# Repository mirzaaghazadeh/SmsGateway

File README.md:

# SmsGateway

**English** · [فارسی](README.fa.md)

A DIY two-SIM **SMS and missed-call gateway**: an ESP32-S3 with two SIM800L GSM modules in a
3D-printed, screwless case, plus a self-hosted Node.js server with a web panel. Build it the way
that suits you: **v1** is hand-wired in a printed case, **v2** puts everything on a PCB in its own
printed case.

| v1: 3D print + hand wiring | v2: PCB + 3D print |
|---|---|
|  |  |

All case images are rendered from the OpenSCAD source in `source/`.

## The idea

This is a hobby project. I carried the idea around for about three years before I finally sat
down and started building it.

It started with a very ordinary problem. After moving to another country, I kept two SIM cards
from home only to receive messages: bank and login codes (OTP), notices, and the odd missed call.
That meant carrying an old phone around just for them, remembering to charge it, and finding its
SMS inbox full at the worst moment, with a code that never arrived.

So I built this for myself: put the SIM cards in one small box that stays plugged in at home and
takes care of them:

- Every SMS that arrives on either SIM goes over Wi-Fi to **your own server**, and so does every
  incoming call (rejected and logged as a missed call).
- You read everything in a **web panel from anywhere**: verification codes, bank messages, who called.
- Or get them in **Telegram**: each SIM can go to its own chats, a one-time code is one tap to copy,
  and a reply to an SMS goes back to its sender from the same SIM. `/stats` answers with the status,
  `/balance` with the balance, and you get an alert when the gateway goes offline or a SIM loses
  the network.
- The SIM cards stay alive: the gateway can check their balance and send an SMS now and then, so
  the operator does not switch off a prepaid SIM that is rarely used. A SIM that is roaming can be
  set to cost nothing: calls ring instead of being hung up, and it sends no SMS.
- Your own apps can **send SMS** through a small HTTP API, or get a **webhook** the moment a
  message arrives.
- It is built from cheap off-the-shelf parts (an ESP32 and two SIM800L modules) in a 3D-printed
  case, and the server is self-hosted: no SMS service subscription, and no third party reading
  your messages.
- The SIM cards never fill up: each SMS is deleted from the card once the server has it.

Later I added what others would need too, so anyone can build one: for the same reason (SIM cards
from another country, codes you must not miss), or simply as a small self-hosted SMS gateway for
their own apps, with the HTTP API, webhooks and Telegram.

## Features

- **Two SIM cards**, each on its own SIM800L, cards slide in from the outside through the front wall.
- **External antennas**: IPEX to SMA bulkhead cables, SMA sockets in the back wall.
- **0.96" OLED** in the lid for status.
- **Screwless case**: snap latches on the lid, snap pins for the boards, crush ribs, no inserts.
- **Powered from 12 V** through two LM2596 bucks (4.0 V for the modems, 5 V for the ESP32). The v2
  PCB adds a fixed 4.0 V regulator, so a mis-set buck cannot reach the modems.
- **Server + web panel** (Node.js, SQLite): SMS inbox/outbox, calls, device status, HTTP API,
  webhooks, Telegram forwarding per SIM, firmware updates over Wi-Fi.
- **Search and export**: filter messages and calls by SIM and days, download them as CSV.
- **Telegram**: forwarding per SIM with filters (only codes, skip senders or words), replies and
  `/send`, `/stats`, `/balance`, alerts.
- **Per SIM**: a name ("Work"), a switch to turn an empty slot off, the mobile network (automatic,
  or one you pick from a search), the balance (USSD code, checked by hand or every few days), a
  keep-alive SMS, and a roaming mode that saves money abroad (calls ring instead of being hung up,
  no SMS goes out).

> **2G only.** The SIM800L is a 2G (GSM) module. Many countries have already switched 2G off.
> Check your operator before you build one, see [2G shutdowns](SHOPPING_LIST.md#6-caution-2g-shutdowns).

## The web panel

Everything the gateway does shows up in a web panel on your own server. (The pictures use made-up
demo data.)

| Messages | Missed calls |
|---|---|
|  |  |
| **Signal** | **Analytics** |
|  |  |
| **Devices** | **Telegram** |
|  |  |
| **SIM cards: name, network, roaming, balance, keep-alive** | **Phone and dark mode** |
|  |   |

## Two ways to build it

| | **v1: 3D print + hand wiring** | **v2: PCB + 3D print** |
|---|---|---|
| How | Each module clicks into its own printed bay and is wired with Dupont jumpers | The modules plug into one carrier PCB, so there are no loose wires |
| You need | A 3D printer and a soldering iron (about 10 joints) | A 3D printer and a PCB order: bare boards you solder (all through-hole), or boards assembled by the factory |
| Case | `case/v1/`, 148.8 x 96.8 x 32.4 mm | `case/v2/`, 113.2 x 105.8 x 35 mm |
| Guide | [ASSEMBLY.md](ASSEMBLY.md) | [pcb/README.md](pcb/README.md) |
| Good for | Building one gateway from parts you already have | A tidier, sturdier box, or building several |

Both use the same modules, OLED, antennas, 12 V jack and adapter, and run the same firmware and
server.

### The v2 carrier PCB

| Top | Bottom |
|---|---|
|  |  |

100 x 100 mm, 2 layers, all through-hole. The modules plug in, so there is no loose wiring. The
SIM800Ls get a fixed 4.0 V from an LM1084 regulator, so a mis-set LM2596 cannot reach them.

**Want assembled boards (PCBA)?** Everything is ready: send
`pcb/sms_gateway_v2_order_package.zip` to a PCB factory. It holds the Gerbers, BOM,
pick-and-place file, assembly drawing and order specs. For bare boards, upload
`pcb/sms_gateway_v2_gerbers.zip`. See [pcb/README.md](pcb/README.md#ordering-everything-is-ready).

## Project status

| Part | State |
|---|---|
| v1 case | Printed and used for the first build: the modules, the OLED and the 12 V jack fit. Antennas not fitted yet |
| v1 wiring | Built and running, one SIM800L on the network. [ASSEMBLY.md](ASSEMBLY.md) has the wiring and a guide for when something does not work |
| v2 PCB | Designed, design check clean (clearances, connections), order files ready. Updated after the first build with a fixed 4.0 V regulator for the SIM800Ls. **Not yet ordered or built** |
| v2 case | Designed, collision-checked against models of the boards. **Not yet printed** |
| Firmware | Runs on real hardware: setup hotspot, pairing, server sync, updates over Wi-Fi, a SIM800L registered on the network. Bench-test sketch included |
| Server | Web panel, HTTP API, webhooks, Telegram, firmware updates from GitHub releases, 46 passing tests. Runs with a real gateway |

## Repository layout

```
case/v1/            v1 (hand-wired) print files: STL + 3MF of every part, renders
case/v1/bambu/      ready-to-print Bambu Studio plates + the process profile
case/v2/            v2 (PCB) print files: STL + 3MF of every part, renders
pcb/                v2 carrier PCB: Gerbers, BOM, pick-and-place, assembly drawing, order package,
                    KiCad file, renders, and make_board.py that generates all of it
source/             OpenSCAD source of both cases (sms_gateway_box_v1.scad, sms_gateway_box_v2.scad)
firmware/           Arduino sketches: sms_gateway (the gateway), sim800_test (bench test)
server/             Node.js server and web panel (Dockerfile for Coolify / Docker)
docs/panel/         screenshots of the web panel (demo data)
ASSEMBLY.md         v1: where every part sits, power and signal wiring, assembly order, troubleshooting
LESSONS.md          mistakes from the first build and how to avoid them
SHOPPING_LIST.md    parts list for both builds, antennas, power notes, SIM cards, 2G shutdowns
```

## Hardware

| Part | Qty |
|---|---|
| ESP32-S3 dev board (YD-ESP32-S3, 2x USB-C, 28 mm wide) | 1 |
| SIM800L module with IPEX antenna socket | 2 |
| LM2596 buck module (43 x 21 mm) | 2 |
| 0.96" SSD1306 I2C OLED, 128x64, 4 pins (VCC GND SCL SDA) | 1 |
| 1000 uF 16 V low-ESR electrolytic capacitor (max 10.5 x 21 mm) | 2 |
| IPEX (u.FL) to SMA-female bulkhead cable, 12-15 cm | 2 |
| GSM antenna, SMA **male** (not RP-SMA) | 2 |
| DC-099 panel jack 5.5 x 2.1 mm + 12 V 2 A adapter | 1 |
| Micro-SIM with voice + SMS, works on 2G, PIN lock off | 2 |
| **v1 only:** resistors 1 k and 3.3 k (RX level dividers), female-female Dupont jumpers 20 cm | 2 + 2, ~20 |
| **v1, recommended:** LM1084IT-ADJ + 120 Ω + 270 Ω + 100 uF for a fixed 4.0 V (see [ASSEMBLY.md](ASSEMBLY.md)) | 1 set |
| **v2 only:** the carrier PCB and its parts (headers, terminal, diode, regulator, LED, resistors), 4 F-F jumpers for the OLED | see [pcb/README.md](pcb/README.md) |

Full list with alternatives and search terms: [SHOPPING_LIST.md](SHOPPING_LIST.md).

## 3D-printed cases

Both cases print in PLA on a 0.4 mm nozzle with no supports, and both are screwless: the lid
clicks on with 4 snap latches.

### v1 case (hand-wired)

| Front | Back |
|---|---|
|  |  |
| **Inside** | **X-ray (lid transparent)** |
|  |  |

Outside size 148.8 x 96.8 x 32.4 mm + 3.2 mm lid.

1. **Fit tests first**: `case/v1/bambu/1_fit_tests_X2D.3mf` (lid latch, LM2596, SIM800L, OLED,
   ESP32, antenna hole + the OLED plug holder). Check every board fits. On the antenna test, fit
   the real SMA connector (body in the pocket inside, washer + nut outside) and screw the antenna on.
2. **Box**: `case/v1/bambu/2_box_X2D.3mf` (opening up).
3. **Lid**: `case/v1/bambu/3_lid_X2D.3mf` (face down). For two colours, drag `v1_lid.stl` and
   `v1_lid_text.stl` into Bambu Studio together, answer "Yes" (one object), give the letters filament 2.

The Bambu projects are set up for a Bambu Lab X2D. For other printers, use the plain `.stl`/`.3mf`
files in `case/v1/`. Settings: 0.20 mm layers, 3 walls, 5 top / 4 bottom shells, 15% gyroid, no
supports (profile: `case/v1/bambu/SMS case 0.20mm @BBL X2D.json`). Print times on an X2D: fit tests
~3 h, box ~6.5 h, lid ~3 h.

### v2 case (PCB)

| Front | Back |
|---|---|
|  |  |
| **Inside** | **X-ray (lid transparent)** |
|  |  |

Outside size 113.2 x 105.8 x 35 mm + 3.2 mm lid. The PCB clicks onto 4 snap pins in its corner
holes, and 10 posts underneath keep it flat when you plug the modules in. The SIM cards go in
through the front wall, USB-C through the right wall, the 12 V jack sits in the left wall (two short
wires to the screw terminal), and the antennas go in the back wall. The OLED clicks into the lid,
with 4 jumpers to the PCB's OLED header.

1. **Fit tests first**: `case/v2/v2_fit_pin.stl` (the PCB snap pin: a corner hole of the PCB must
   click over it), `v2_fit_latch.stl` and `v2_fit_ant.stl` (same as v1).
2. **Box**: `case/v2/v2_base.stl` (opening up).
3. **Lid**: `case/v2/v2_lid.stl` (face down). For two colours, load `v2_lid_text.stl` with it as
   one object and give the letters filament 2. The OLED plug holder is `v2_dupont4.stl`.

Same print settings as v1.

### Changing sizes

Each case comes from its own file: `source/sms_gateway_box_v1.scad` or
`source/sms_gateway_box_v2.scad` (OpenSCAD 2021.01 or newer). Edit the numbers at the top, then
export a part from the command line:

```sh
openscad -D 'part="base"' -o v1_base.stl source/sms_gateway_box_v1.scad
openscad -D 'part="base"' -o v2_base.stl source/sms_gateway_box_v2.scad
```

v1 parts: `base`, `lid`, `lid_text`, `dupont4` (OLED plug holder), `fit_latch`, `fit_ant`,
`fit_buck`, `fit_esp`, `fit_sim`, `fit_oled`, `fittest`. v2 parts: `base`, `lid`, `lid_text`,
`dupont4`, `fit_pin`, `fit_latch`, `fit_ant`. Previews: `assembly`, `exploded`, `closed`.
`check` shows any part of a board that runs into the case; it must come out empty.

| If... | Change |
|---|---|
| The lid is too hard to open / falls off | `latch_e` (0.8): lower to 0.6 / raise to 1.0 |
| A SIM800L is too tight / loose in its bay | `sim_rib` (0.45): lower / raise |
| A thick USB-C plug does not click in | `usb_plug` (recess size), e.g. `[14, 8]` |
| You use a DC-022B jack instead of DC-099 | `dc_d` = 8.2 (11.2 for DC-099) |
| The OLED pegs miss its holes | measure the hole spacing into `oled_hole` |
| The OLED snap pins break | v1: `oled_snap = false` for plain pegs, melt the tips with a soldering iron |
| v2: the SIM card misses the holder | `sim_card_z` (card height), or `sock_h` / `pin_h` if your headers are taller or shorter than 8.5 / 2.5 mm |
| v2: the USB-C plugs do not reach the sockets | `usb_zc` (socket height), `usb_extra` (opening size) |
| v2: the PCB is too tight / loose on its snap pins | `pcb_pin` (shaft, barb, slot) |

**Not measured yet** (estimated from photos and maker CAD models, print the fit tests first):
OLED hole spacing (22.9 x 23.3), LM2596 hole and pad positions, SIM800L board size (25 x 23),
capacitor size, and for v2 the height of the plugged-in modules. Fit-test results and fixes are
welcome as issues or pull requests.

## Wiring

**v2:** the PCB does all of it, with the same pins as below. You only add the two 12 V wires from
the jack to the screw terminal and the 4 OLED jumpers.

**v1:** every wire, pin by pin ([full size](docs/wiring_v1.png), [SVG](docs/wiring_v1.svg)):

<p align="center">
  
</p>

[ASSEMBLY.md](ASSEMBLY.md) has the same as tables. In short:

- 12 V jack to both LM2596 inputs. **Set the outputs before connecting anything**: A = 4.0 V (both
  SIM800Ls, never above 4.2 V), B = 5.0 V (ESP32). A new LM2596 can output almost 12 V, and 12 V
  kills a SIM800L at once. Lock the trimmers with a drop of nail polish, or add the fixed 4.0 V
  regulator described in ASSEMBLY.md.
- A 1000 uF capacitor soldered at each SIM800L's VCC/GND (2 A transmit bursts).
- ESP32 TX to SIM800L RXD through a 1 k / 3.3 k divider; SIM800L TXD straight to the ESP32 RX.
- SIM1: GPIO17 TX, GPIO18 RX, GPIO5 RST. SIM2: GPIO15 TX, GPIO16 RX, GPIO6 RST. OLED: GPIO8 SDA, GPIO9 SCL.
- SIM800L pins in header order: NET VCC RST RXD TXD GND. Micro-SIM, gold contacts toward the board.

Something not working ("not answering", "no SIM card", no light on the SIM800L)? See
[ASSEMBLY.md → When something does not work](ASSEMBLY.md#when-something-does-not-work).

**Before you build, read [LESSONS.md](LESSONS.md)**: the mistakes made on the first build (a 12 V
spark that killed two SIM800Ls, resistors in the wrong place, a SIM card upside down, a server that
forgot everything on each deploy) and how to avoid them.

## Firmware

### Gateway: `firmware/sms_gateway/`

The program for the ESP32-S3 in the box. It runs both SIM800L modules, shows the status on the
OLED and the RGB LED, and syncs with the server, which does all the SMS work.
Full guide: [firmware/sms_gateway/README.md](firmware/sms_gateway/README.md).

- Arduino IDE 2 with the "esp32" core by Espressif (tested with 3.0.7), plus the **ArduinoJson 7**
  and **Adafruit SSD1306** libraries.
- Board "ESP32S3 Dev Module", Flash 16MB, Partition "16M Flash (3MB APP/9.9MB FATFS)", PSRAM "OPI
  PSRAM". Upload through the USB-C port marked COM.
- **First setup**: the gateway opens a `SMS-Gateway-XXXX` hotspot (password `smsgateway`). Join it
  with your phone, choose your Wi-Fi and enter your server address. The page and the OLED show the
  gateway's own **device key**: add it in the panel under Devices → Add a gateway.
- **Up to 5 Wi-Fi networks**: the gateway joins whichever saved network is in range. Add them on the
  setup page, or from the panel (Devices → Wi-Fi networks) before you move the gateway.
- **No open hotspot once set up**: change settings from the panel (Devices → Open settings page:
  the page opens on the gateway's own Wi-Fi only) or press BOOT briefly on the gateway.
- **Hold BOOT for 5 s** to erase the Wi-Fi and server settings and open the setup hotspot again
  (the device key stays, so the panel keeps knowing the gateway).

### Bench test: `firmware/sim800_test/`

Tests one ESP32-S3 + one SIM800L before anything goes in the box: it checks UART, supply voltage,
SIM, network registration and signal, prints PASS/FAIL with hints, then works as an AT terminal
(`!sms +<number> text` sends a test SMS). Serial Monitor at 115200 baud; wiring is in the comment
at the top of the sketch.

## Server

Node.js 24+ server and web panel in `server/`. No npm dependencies: Node's built-in `http`,
`crypto` and `node:sqlite`, and a vanilla-JS panel with hand-made SVG charts.
Full guide (Coolify steps, API, webhooks, data retention): [server/README.md](server/README.md).

```sh
cd server
ADMIN_PASSWORD=change-me npm start   # web panel on http://localhost:3000
npm test
```

**Deploy with Docker Compose** (e.g. Coolify): `docker-compose.yaml` at the repository root builds
`server/` and keeps the SQLite database in the named volume `gateway-data` (mounted at `/data`), so
it survives redeploys. In Coolify use the Build Pack "Docker Compose" and set the service domain
with the port, like `https://sms.example.com:3000`. Plain Docker: `ADMIN_PASSWORD=change-me docker compose up -d`.

| Env var | |
|---|---|
| `ADMIN_PASSWORD` | panel login; if unset, one is generated and printed in the logs |
| `API_KEY` | optional; generated and shown in the panel's Settings if unset |
| `SESSION_SECRET` | optional |
| `PORT`, `DATA_DIR` | default 3000 and `./data` (`/data` in Docker) |

**Device protocol**: the ESP32 sends `POST /api/device/sync` with `Authorization: Bearer <its device key>`
(the key the gateway made itself and the owner added under Devices) every few seconds, with device and SIM status plus events (incoming SMS as raw PDUs, missed calls,
job results). The reply carries the jobs to run (outgoing SMS as ready-made PDUs, AT commands,
restart). All SMS encoding and decoding (GSM-7 / UCS-2, multipart) happens on the server.

**Public API** for other apps, `Authorization: Bearer <API_KEY>`:

| | |
|---|---|
| `POST /api/v1/sms` | send: `{"to": "+15551234567", "text": "Hello", "sim": 0}` (`sim` 0 = any, 1, 2) |
| `GET /api/v1/sms/:id` | status of one message |
| `GET /api/v1/messages?direction=in&since_id=` | inbox / outbox (filters: `sim`, `device`, `since`, `until`, `q`) |
| `GET /api/v1/calls` | missed calls (same filters) |
| `GET /api/v1/messages.csv`, `GET /api/v1/calls.csv` | the same as a CSV file |
| `GET /api/v1/status` | gateway and SIM status, with the last balance |

**Webhooks** (URL set in the panel): `sms.received`, `sms.sent`, `sms.failed`, `call.missed`,
`device.offline`, `device.online`, signed with HMAC-SHA256 in the `X-Gateway-Signature` header.

**Telegram** (Settings → Telegram): paste a bot token from @BotFather and choose, for each SIM,
the chats that get its SMS and missed calls, all of them or only one-time codes. A long SMS
arrives as one message, joined from its parts. Reply to an SMS to answer it from the same SIM, or
send `/send +15551234567 text`. Send `/stats` for the status of every gateway and SIM, `/balance`
for the balance, and turn on alerts for a gateway that goes offline or a SIM that loses the
network. The bot can delete its own messages after 1 hour to 2 days (the most Telegram allows a
bot). The server does all of this; the gateway does not talk to Telegram. Details in
[server/README.md](server/README.md#telegram).

## Contributing

Issues and pull requests are welcome, especially fit-test photos of the cases, reports from a
built v2 PCB, reports from running the firmware on real hardware, and support for 4G modules
(A7670 and similar) for countries without 2G.

## License

[MIT](LICENSE)

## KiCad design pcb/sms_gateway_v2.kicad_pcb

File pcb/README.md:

# SMS Gateway v2: the carrier PCB

v2 is the PCB build of the gateway. The modules plug into one board, so there is no loose wiring:
the ESP32-S3 dev board, both SIM800Ls, both LM2596s and the OLED. It goes into the v2 case
(`case/v2/`). The firmware and the server are the same for v1 and v2.

| Top | Bottom |
|---|---|
|  |  |

- 100 x 100 mm, 2 layers, 1.6 mm, **all through-hole**, so it is easy to solder by hand.
- Same pins as the firmware: SIM1 TX 17 / RX 18 / RST 5, SIM2 TX 15 / RX 16 / RST 6,
  OLED SDA 8 / SCL 9.
- 12 V comes in on a screw terminal, through a 1N5822 diode that protects against reversed
  polarity, to both LM2596s: A (5.5 V) for the SIM800Ls, B (5.0 V) for the ESP32.
- **The SIM800Ls get a fixed 4.06 V** from U3, an LM1084 regulator behind LM2596 A. Whatever A's
  trimmer is set to, up to the full 12 V, the SIM800Ls (4.4 V max) are safe. On the first
  hand-wired build an LM2596 turned up to 12 V killed both modules; this is the fix.
- The 1000 uF capacitors and the 1k / 3.3k RX dividers are on the board.
- **JP1** connects the 5 V of LM2596 B to the ESP32. Take the jumper off when the ESP32 runs on
  USB only.
- Ground fill on both sides. The design check finds no errors: every gap is at least 0.25 mm, and
  every connection is complete.

## Ordering: everything is ready

You can order bare boards and solder them yourself, or order them **assembled (PCBA)** by the
factory. Everything a factory needs is already in this folder.

**Bare boards.** Upload `sms_gateway_v2_gerbers.zip` to any PCB maker (JLCPCB, PCBWay, ...) and keep
the defaults: 2 layers, 1.6 mm, HASL, any colour. 5 or 10 boards of this size usually cost a few
dollars plus shipping.

**Assembled boards (PCBA).** Send `sms_gateway_v2_order_package.zip` to the factory. It holds:

| File | What |
|---|---|
| `sms_gateway_v2_order_specs.txt` | Board and assembly specs, written as a request for a quote |
| `sms_gateway_v2_gerbers.zip` | Gerber and drill files |
| `sms_gateway_v2_BOM.xlsx` (`.csv`) | Parts list with values, packages, polarity notes |
| `sms_gateway_v2_pick_and_place.xlsx` (`.csv`) | Where each part sits (origin bottom-left, mm) |
| `sms_gateway_v2_assembly_drawing.pdf` | Drawing with part names, polarity arrows and "do not place" marks |
| `render_top.png`, `render_bottom.png` | Pictures of the board |

Notes for the order:

- All parts are through-hole. Chinese factories call through-hole assembly **"DIP"**. There are
  20 parts and 91 solder joints per board, and no stencil is needed.
- The factory buys all the parts ("turnkey"). The **LM2596 modules are marked "do not place"**,
  since you set their voltage yourself. The specs ask for an optional extra price for fitting them.
- The ESP32 board and the SIM800Ls are not part of the order. They plug in later.
- Write your country in the specs file (the "shipping cost to" line) before you send it.
- Ask for a photo of the first board before they ship.

A message you can send with the zip:

> Hello, please quote PCB fabrication + turnkey assembly for the attached design, 10 pcs (and 20).
> 2 layers, FR-4, 100 x 100 mm, 1.6 mm, 1 oz, HASL, green/white. Assembly: all through-hole (DIP),
> top side only, 20 parts / 91 solder joints per board, you source all parts (equivalents OK).
> U1/U2 are not placed. Details are in the specs file and the assembly drawing. Please also quote
> the bare PCB, the lead time and the shipping.

## Building it yourself

1. Solder the low parts first: R1-R7 (no polarity; R6 = 120 Ω, R7 = 270 Ω), D1 (band = cathode at
   the square pad), the LED (short leg in the square pad), then C1/C2/C3 (+ leg in the square pad).
   **U3 lies flat** in its outline: bend its three legs 90° about 3 mm from the body, plastic face
   down and metal tab up, pin 1 (ADJ) in the square pad. No heatsink, no screw.
2. The headers: J1 and J2 for the ESP32 (1x22 female; **J2 goes in the outer hole row**, the one
   at the board edge, for the 28 mm wide YD-ESP32-S3; use the inner row only for a 25.4 mm wide
   board), J3/J4 for the SIM800Ls (1x6 female), J6 for the OLED (1x4 male), JP1 (1x2 male + jumper)
   and the screw terminal J5.
3. The two LM2596 modules: put 4 single male header pins into the board's corner holes, plastic
   spacer down, set the module on them and solder both sides. **Line up the IN+ / OUT+ labels on
   the PCB with the labels on the module.**
4. **Set the voltages with nothing plugged in:** connect 12 V and turn the trimmers until
   LM2596 A reads **5.5 V** and B reads **5.0 V** on their OUT+ / OUT- pads (5.3-6 V for A is fine).
   Then check the SIM supply: **4.0-4.1 V** between VCC and GND of a SIM800L socket (J3/J4). Lock
   both trimmers with a drop of nail polish.
5. Plug in the modules. The ESP32 goes in with its USB-C at the right edge. The SIM800Ls go in
   chip up and pins down, with the SIM card edge at the board edge. Their 6-pin header must be
   soldered pointing **down**, on the SIM-holder side. Connect the OLED with 4 F-F jumpers
   (SDA-SDA, SCL-SCL, GND-GND, 3V3-VCC).

The board clicks into the v2 case (`case/v2/`, see the main README) on 4 snap pins.

## Check before you order

Some sizes are estimates, the same ones the v1 case uses. Print `render_top.png` at 100 % and lay
your real modules on it.

- **ESP32 row spacing.** 25.4 mm for the YD-ESP32-S3, 22.86 mm for Espressif's drawing. The board
  has holes for both.
- **SIM800L header position.** 1.9 mm from the module edge, with NET 5 mm from the SIM card edge.
  This only changes where the module overhangs, not the wiring.
- **LM2596 corner pads.** 39.6 x 17.4 mm apart. If yours differ, bend the pin legs or use short
  wires.

## Files and regenerating

Everything here is generated by `make_board.py`: the board layout, the routing, the ground fill,
the design check and every output file. Edit it and run it again:

```sh
pip install shapely matplotlib numpy openpyxl
python3 make_board.py
```

`render_nets.png` shows every connection in its own colour, which is handy for checking a change.
`sms_gateway_v2.kicad_pcb` is written for editing in KiCad 8 or newer. It has not been opened in
KiCad yet, so press B to fill the ground zones after loading. The Gerber files are the reference.

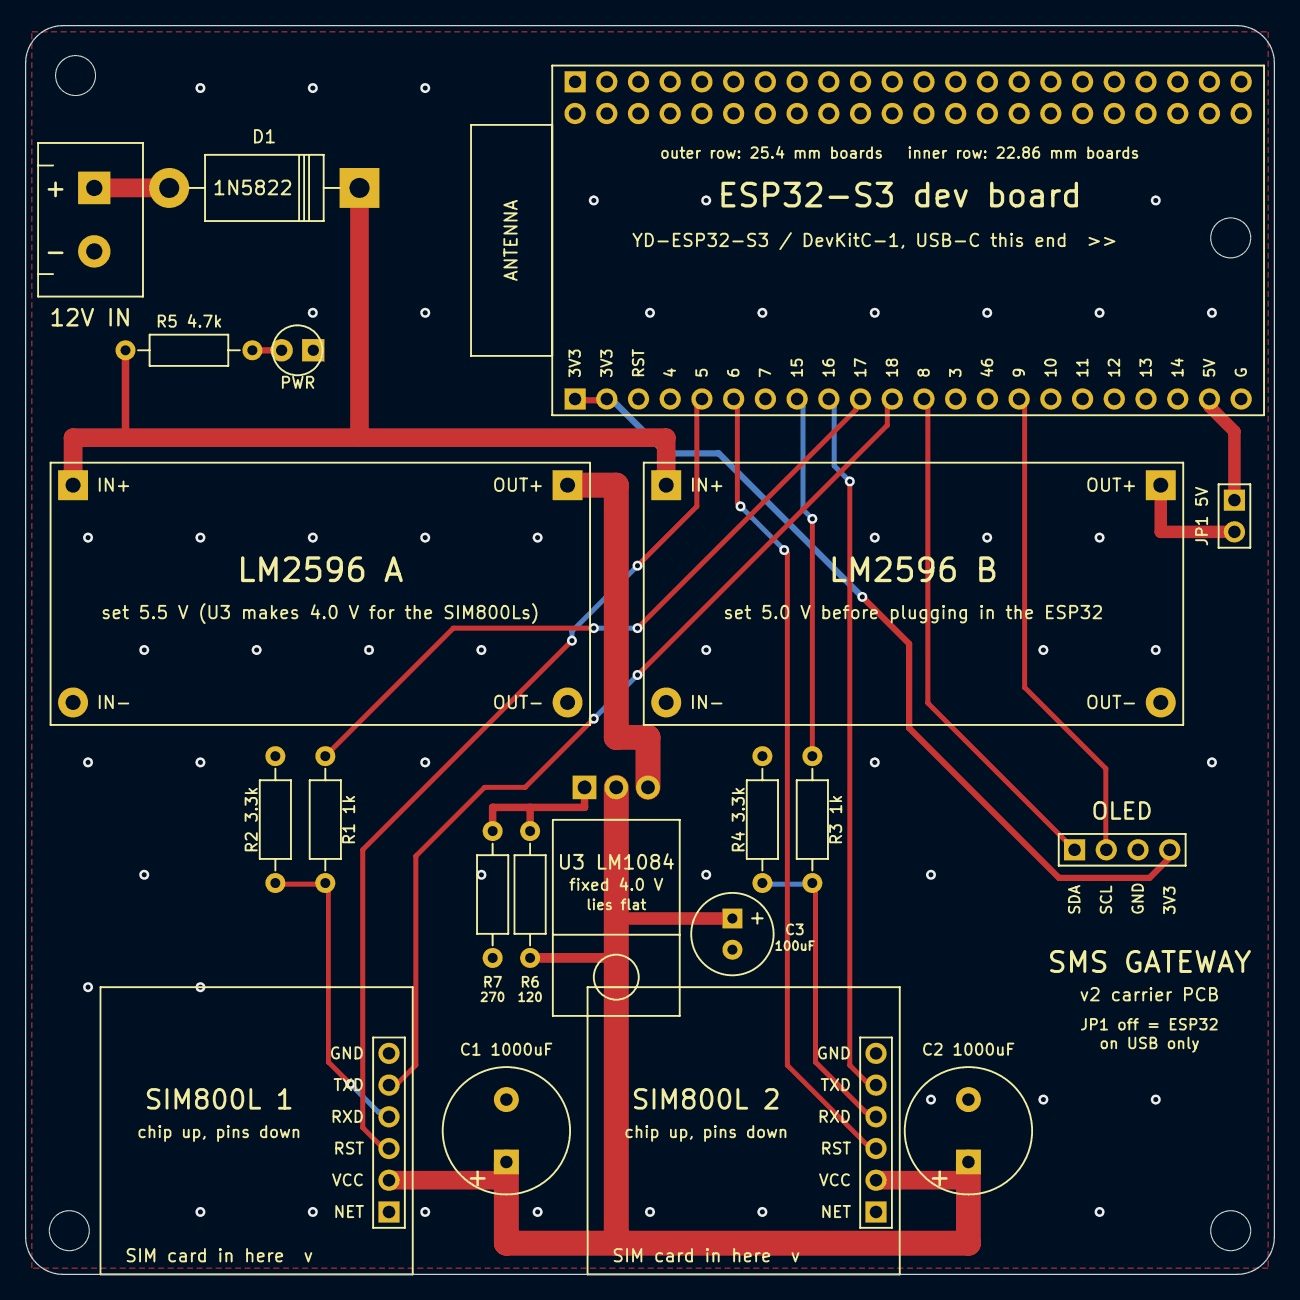
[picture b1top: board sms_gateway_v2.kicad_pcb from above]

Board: 2 copper layers, 100.0 x 100.0 mm, 26 parts (0 on the bottom side), 20 nets.

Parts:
C1, C2: 1000uF; CP_Radial_D10.0mm_P5.00mm
C3: 100uF; CP_Radial_D6.3mm_P2.50mm
D1: 1N5822; D_DO-201AD_P15.24mm_Horizontal
D2: LED; LED_D3.0mm
H1, H2, H3, H4: M3; MountingHole_3.2mm_M3
J1: 1x22 female header; PinSocket_1x22_P2.54mm
J2: 1x22 female header; PinSocket_1x22_P2.54mm_2rows
J3, J4: 1x6 female header; PinSocket_1x06_P2.54mm
J5: 12V IN; TerminalBlock_1x02_P5.08mm
J6: OLED; PinHeader_1x04_P2.54mm
JP1: 5V ESP; PinHeader_1x02_P2.54mm
R1, R3: 1k; R_Axial_DIN0207_L6.3mm_D2.5mm_P10.16mm
R2, R4: 3.3k; R_Axial_DIN0207_L6.3mm_D2.5mm_P10.16mm
R5: 4.7k; R_Axial_DIN0207_L6.3mm_D2.5mm_P10.16mm
R6: 120; R_Axial_DIN0207_L6.3mm_D2.5mm_P10.16mm
R7: 270; R_Axial_DIN0207_L6.3mm_D2.5mm_P10.16mm
U1, U2: LM2596 module; LM2596_module_43x21
U3: LM1084-ADJ; TO-220-3_Horizontal_TabUp

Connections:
+3V3: J1.1, J1.2, J6.4
+4V: C1.1, C2.1, C3.1, J3.2, J4.2, R6.2, U3.2
+5V5: U1.OUT+, U3.3
+5V_BUCK: JP1.2, U2.OUT+
+5V_ESP: J1.21, JP1.1
+12V: D1.1, R5.1, U1.IN+, U2.IN+
ADJ: R6.1, R7.1, U3.1
GND: C1.2, C2.2, C3.2, D2.1, J1.22, J2.1, J2.21, J2.22, J3.6, J4.6, J5.2, J6.3, R2.2, R4.2, R7.2, U1.IN-, U1.OUT-, U2.IN-, U2.OUT-
LED_A: D2.2, R5.2
S1_RST: J1.5, J3.3
S1_RXD: J3.4, R1.2, R2.1
S1_TX: J1.10, R1.1
S1_TXD: J1.11, J3.5
S2_RST: J1.6, J4.3
S2_RXD: J4.4, R3.2, R4.1
S2_TX: J1.8, R3.1
S2_TXD: J1.9, J4.5
SCL: J1.15, J6.2
SDA: J1.12, J6.1
VIN: D1.2, J5.1

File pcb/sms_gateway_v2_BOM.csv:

Item,Designator,Qty per board,Value,Description,Package,Mounting,Suggested part (equivalent OK),Place,Notes
1,"J1,J2",2,"Female header 1x22","2.54 mm pitch, single row, straight, 8.5 mm high","THT 1x22 P2.54","THT","Any brand","Yes","J2: solder into the OUTER hole row only (row at the board edge). Inner row stays empty."
2,"J3,J4",2,"Female header 1x6","2.54 mm pitch, single row, straight, 8.5 mm high","THT 1x6 P2.54","THT","Any brand","Yes",""
3,"J6",1,"Male pin header 1x4","2.54 mm pitch, single row, straight","THT 1x4 P2.54","THT","Any brand","Yes",""
4,"JP1",1,"Male pin header 1x2 + jumper cap","2.54 mm pitch, straight","THT 1x2 P2.54","THT","Any brand","Yes","Fit the jumper cap on JP1."
5,"J5",1,"Screw terminal 2-pin","5.0 / 5.08 mm pitch, wire entry toward the left board edge","THT P5.08","THT","KF301-5.0-2P or DG301-5.0-02P","Yes",""
6,"D1",1,"1N5822","Schottky diode 3 A 40 V","DO-201AD, 15.24 mm lead spacing","THT","1N5822 (any brand)","Yes","Polarity: band (cathode) on the SQUARE pad."
7,"D2",1,"LED 3 mm red","3 mm LED, diffused","THT 3 mm, 2.54 mm leads","THT","Any brand","Yes","Polarity: short leg (cathode, flat side) in the SQUARE pad."
8,"C1,C2",2,"1000 uF 16 V","Aluminium electrolytic, low ESR, 105 C, D10 mm x 16-20 mm","Radial D10, 5.0 mm lead spacing","THT","Any brand, low ESR","Yes","Polarity: + leg in the SQUARE pad (marked +)."
9,"C3",1,"100 uF 16 V","Aluminium electrolytic, 105 C, D6.3 mm","Radial D6.3, 2.5 mm lead spacing","THT","Any brand","Yes","Polarity: + leg in the SQUARE pad (marked +)."
10,"U3",1,"LM1084IT-ADJ","Adjustable low-dropout regulator 5 A","TO-220-3, lying flat (horizontal)","THT","LM1084IT-ADJ, LD1084V or LM1085IT-ADJ (pins ADJ-OUT-IN)","Yes","Lies flat in its outline: legs bent 90 deg, plastic face down, metal tab up. Pin 1 (ADJ) in the SQUARE pad. No heatsink, no screw."
11,"R6",1,"120 Ohm","Resistor 1/4 W 1 % metal film","Axial, 10.16 mm lead spacing","THT","Any brand","Yes","With R7 sets U3 to 4.06 V. Use 1 % parts."
12,"R7",1,"270 Ohm","Resistor 1/4 W 1 % metal film","Axial, 10.16 mm lead spacing","THT","Any brand","Yes",""
13,"R1,R3",2,"1 kOhm","Resistor 1/4 W 1 % metal film","Axial, 10.16 mm lead spacing","THT","Any brand","Yes",""
14,"R2,R4",2,"3.3 kOhm","Resistor 1/4 W 1 % metal film","Axial, 10.16 mm lead spacing","THT","Any brand","Yes",""
15,"R5",1,"4.7 kOhm","Resistor 1/4 W 1 % metal film","Axial, 10.16 mm lead spacing","THT","Any brand","Yes",""
16,"U1,U2",2,"LM2596 buck module","Blue DC-DC module 43 x 21 mm","4 corner pads","THT","-","NO (DNP)","Do not place. Optional extra quote: supply and solder 2 modules on 4 straight header pins each."
